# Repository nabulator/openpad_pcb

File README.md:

# openpad_pcb
A pcb for home DIY travelpads, ddr/itg/stepmaniax pads

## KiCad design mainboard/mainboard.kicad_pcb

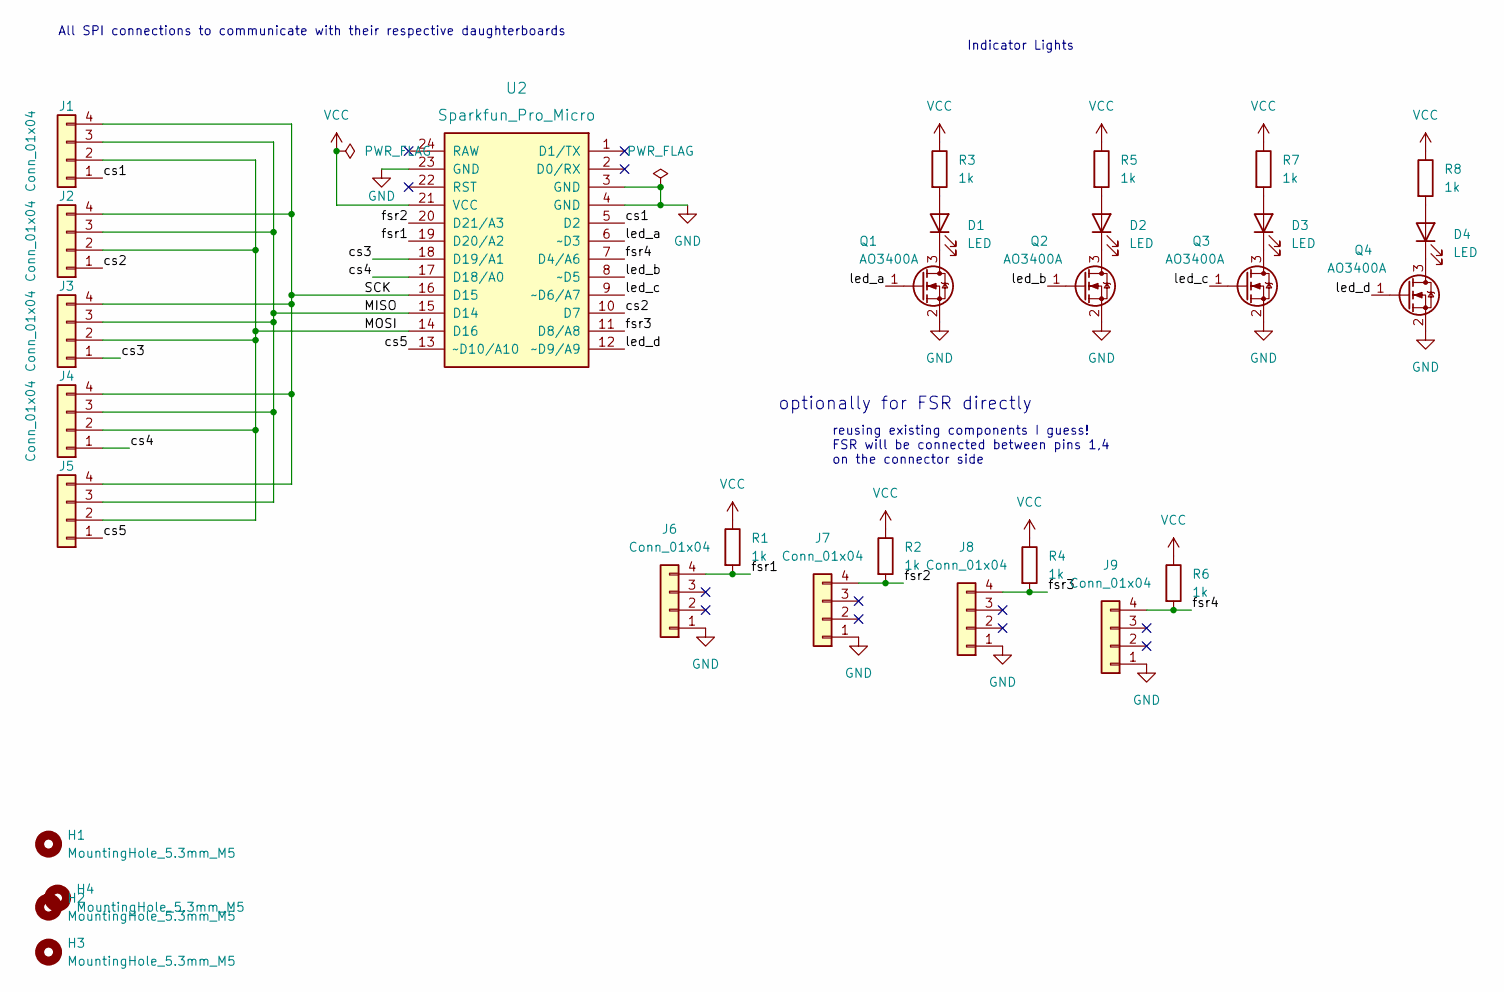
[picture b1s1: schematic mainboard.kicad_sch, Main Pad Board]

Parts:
D1, D2, D3, D4: LED; LED_1210_3225Metric_Pad1.42x2.65mm_HandSolder
H1, H2, H3, H4: MountingHole_5.3mm_M5
J1, J2, J3, J4, J6, J7, J8, J9: Conn_01x04; PinHeader_1x04_P2.54mm_Horizontal
J5: (no value)
Q1, Q2, Q3, Q4: AO3400A; SOT-23
R1, R2, R3, R4, R5, R6, R7, R8: 1k; R_1206_3216Metric_Pad1.30x1.75mm_HandSolder
U2: Sparkfun_Pro_Micro

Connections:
/MISO: J1.3, J2.3, J3.3, J4.3, J5.3, U2.15 (D14)
/MOSI: J1.2, J2.2, J3.2, J4.2, J5.2, U2.14 (D16)
/SCK: J1.4, J2.4, J3.4, J4.4, J5.4, U2.16 (D15)
/cs1: J1.1, U2.5 (D2)
/cs2: J2.1, U2.10 (D7)
/cs3: J3.1, U2.18 (D19/A1)
/cs4: J4.1, U2.17 (D18/A0)
/cs5: J5.1, U2.13 (~D10/A10)
/fsr1: J6.4, R1.2, U2.19 (D20/A2)
/fsr2: J7.4, R2.2, U2.20 (D21/A3)
/fsr3: J8.4, R4.2, U2.11 (D8/A8)
/fsr4: J9.4, R6.2, U2.7 (D4/A6)
/led_a: Q1.1 (G), U2.6 (~D3)
/led_b: Q2.1 (G), U2.8 (~D5)
/led_c: Q3.1 (G), U2.9 (~D6/A7)
/led_d: Q4.1 (G), U2.12 (~D9/A9)
GND: J6.1, J7.1, J8.1, J9.1, Q1.2 (S), Q2.2 (S), Q3.2 (S), Q4.2 (S), U2.3 (GND), U2.4 (GND), U2.23 (GND)
unnamed: D1.1 (K), Q1.3 (D)
unnamed: D1.2 (A), R3.2
unnamed: D2.1 (K), Q2.3 (D)
unnamed: D2.2 (A), R5.2
unnamed: D3.1 (K), Q3.3 (D)
unnamed: D3.2 (A), R7.2
unnamed: D4.1 (K), Q4.3 (D)
unnamed: D4.2 (A), R8.2
VCC: R1.1, R2.1, R3.1, R4.1, R5.1, R6.1, R7.1, R8.1, U2.21 (VCC)

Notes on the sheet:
optionally for FSR directly
All SPI connections to communicate with their respective daughterboards
Indicator Lights
reusing existing components I guess! FSR will be connected between pins 1,4 on the connector side

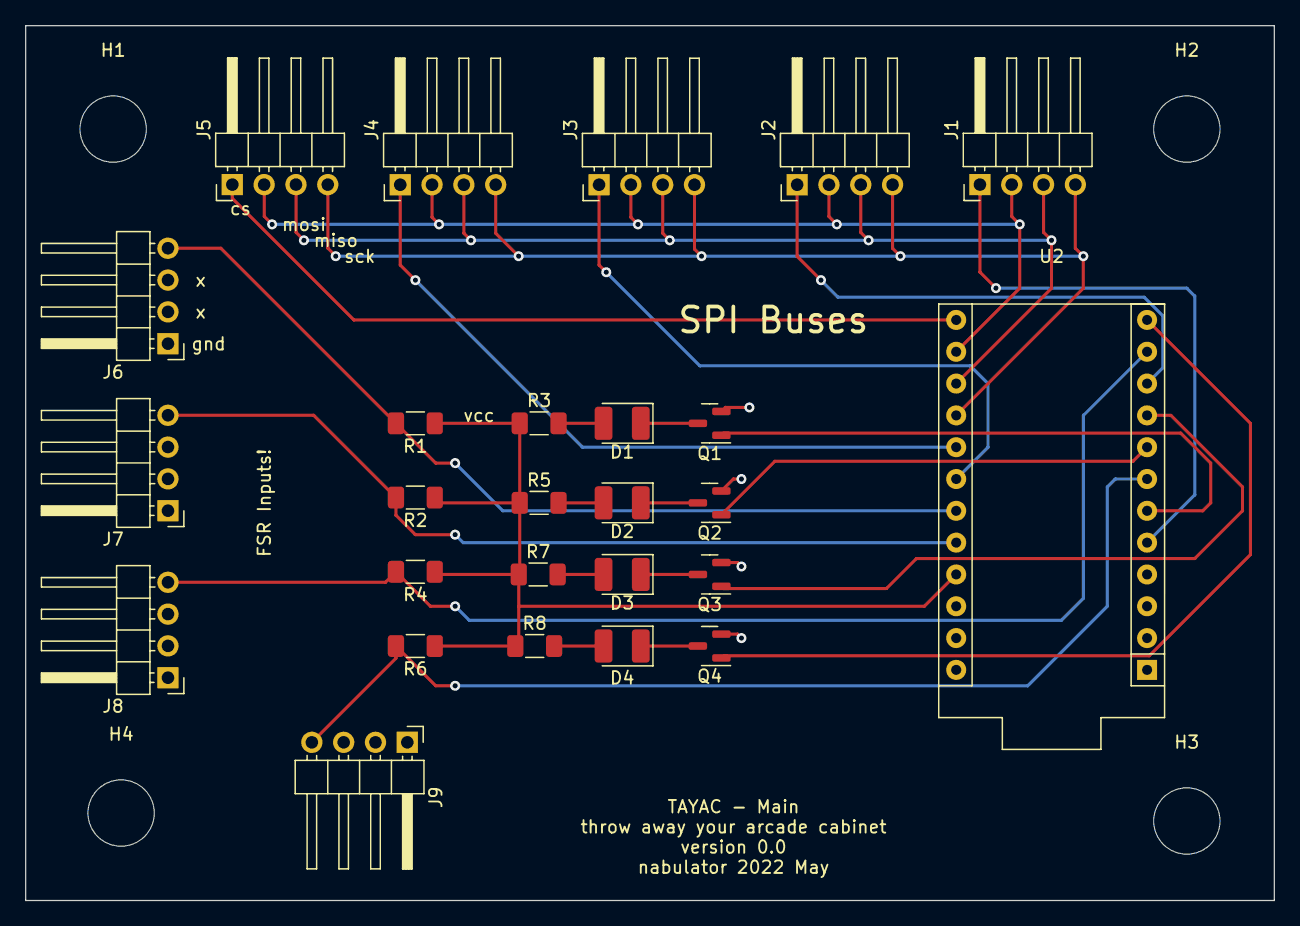
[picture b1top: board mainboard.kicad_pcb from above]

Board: 2 copper layers, 99.7 x 69.8 mm, 31 parts (1 on the bottom side), 26 nets.

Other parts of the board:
G1: LOGO; arrow_graphic

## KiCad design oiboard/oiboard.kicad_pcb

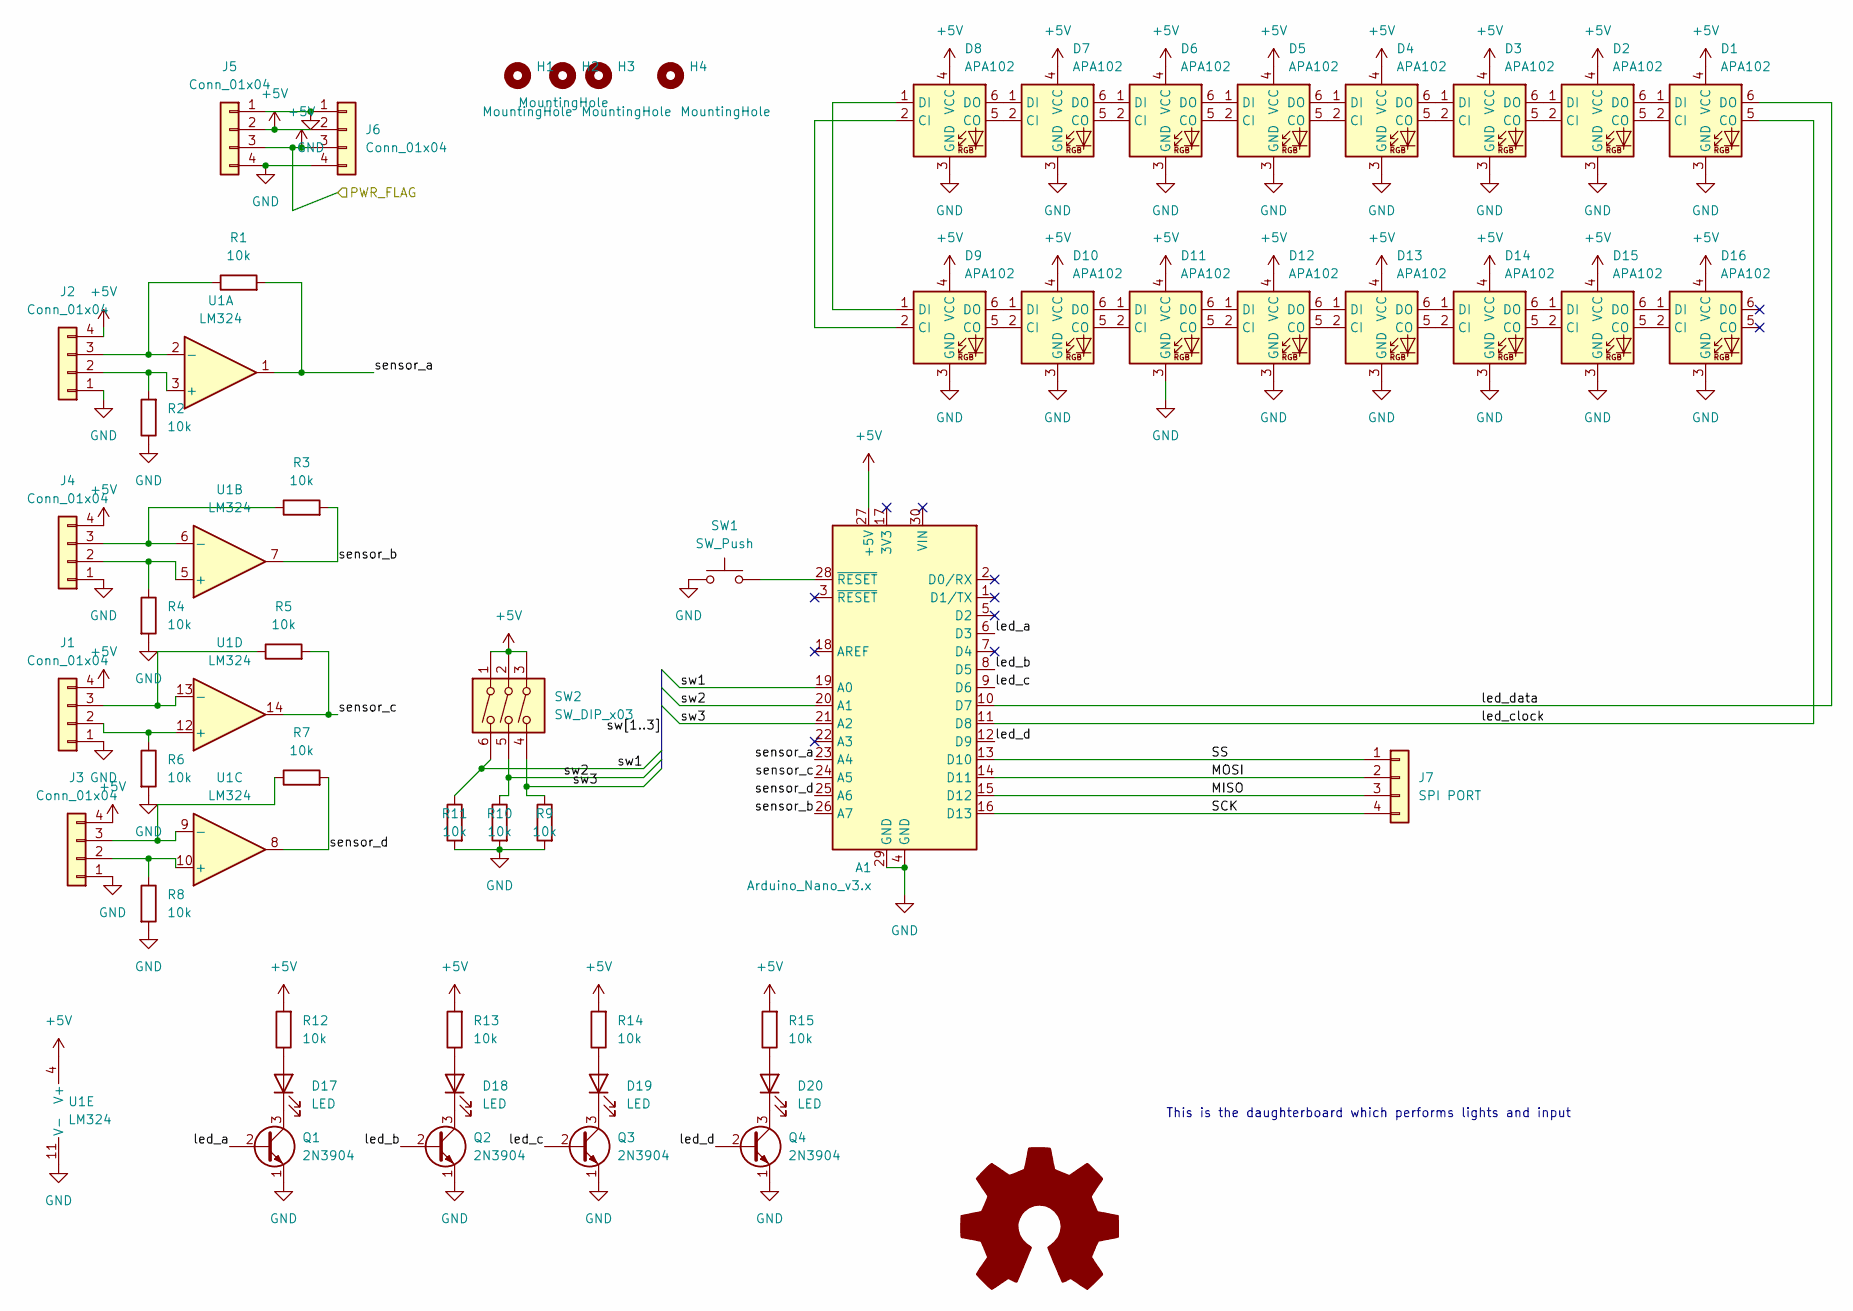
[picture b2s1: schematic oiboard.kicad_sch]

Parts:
A1: Arduino_Nano_v3.x; Arduino_Nano
D1, D2, D3, D4, D5, D6, D7, D8, D9, D10, D11, D12, D13, D14, D15, D16: APA102; LED_RGB_5050-6
D17, D18, D19, D20: LED; LED_D5.0mm
H1, H2, H3, H4: MountingHole; MountingHole_3mm
J1, J2, J3, J4: Conn_01x04; PinHeader_1x04_P2.54mm_Horizontal
J5, J6: Conn_01x04; TerminalBlock_bornier-4_P5.08mm
J7: SPI PORT; PinHeader_1x04_P2.54mm_Horizontal
Q1, Q2, Q3, Q4: 2N3904; TO-92_Inline
R1, R2, R3, R4, R5, R6, R7, R8, R9, R10, R11, R12, R13, R14, R15: 10k; R_Axial_DIN0207_L6.3mm_D2.5mm_P10.16mm_Horizontal
SW1: SW_Push; SW_PUSH_6mm
SW2: SW_DIP_x03; SW_DIP_SPSTx03_Slide_9.78x9.8mm_W7.62mm_P2.54mm
U1: LM324; DIP-14_W7.62mm

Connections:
+5V: A1.27 (+5V), D1.4 (VCC), D2.4 (VCC), D3.4 (VCC), D4.4 (VCC), D5.4 (VCC), D6.4 (VCC), D7.4 (VCC), D8.4 (VCC), D9.4 (VCC), D10.4 (VCC), D11.4 (VCC), D12.4 (VCC), D13.4 (VCC), D14.4 (VCC), D15.4 (VCC), D16.4 (VCC), J1.4, J2.4, J3.4, J4.4, J5.2, J5.3, J6.2, J6.3, R12.2, R13.2, R14.2, R15.2, SW2.1, SW2.2, SW2.3, U1.4 (V+)
/MISO: A1.15 (D12), J7.3
/MOSI: A1.14 (D11), J7.2
/SCK: A1.16 (D13), J7.4
/SS: A1.13 (D10), J7.1
/led_a: A1.6 (D3), Q1.2 (B)
/led_b: A1.8 (D5), Q2.2 (B)
/led_c: A1.9 (D6), Q3.2 (B)
/led_clock: A1.11 (D8), D1.5 (CO)
/led_d: A1.12 (D9), Q4.2 (B)
/led_data: A1.10 (D7), D1.6 (DO)
/sensor_a: A1.23 (A4), R1.2, U1.1
/sensor_b: A1.26 (A7), R3.2, U1.7
/sensor_c: A1.24 (A5), R5.2, U1.14
/sensor_d: A1.25 (A6), R7.2, U1.8
/sw1: A1.19 (A0), R11.1, SW2.6
/sw2: A1.20 (A1), R10.1, SW2.5
/sw3: A1.21 (A2), R9.1, SW2.4
GND: A1.4 (GND), A1.29 (GND), D1.3 (GND), D2.3 (GND), D3.3 (GND), D4.3 (GND), D5.3 (GND), D6.3 (GND), D7.3 (GND), D8.3 (GND), D9.3 (GND), D10.3 (GND), D11.3 (GND), D12.3 (GND), D13.3 (GND), D14.3 (GND), D15.3 (GND), D16.3 (GND), J1.1, J2.1, J3.1, J4.1, J5.1, J5.4, J6.1, J6.4, Q1.1 (E), Q2.1 (E), Q3.1 (E), Q4.1 (E), R2.1, R4.2, R6.2, R8.2, R9.2, R10.2, R11.2, SW1.1, U1.11 (V-)
unnamed: A1.28 (~RESET), SW1.2
unnamed: D1.1 (DI), D2.6 (DO)
unnamed: D1.2 (CI), D2.5 (CO)
unnamed: D2.1 (DI), D3.6 (DO)
unnamed: D2.2 (CI), D3.5 (CO)
unnamed: D3.1 (DI), D4.6 (DO)
unnamed: D3.2 (CI), D4.5 (CO)
unnamed: D4.1 (DI), D5.6 (DO)
unnamed: D4.2 (CI), D5.5 (CO)
unnamed: D5.1 (DI), D6.6 (DO)
unnamed: D5.2 (CI), D6.5 (CO)
unnamed: D6.1 (DI), D7.6 (DO)
unnamed: D6.2 (CI), D7.5 (CO)
unnamed: D7.1 (DI), D8.6 (DO)
unnamed: D7.2 (CI), D8.5 (CO)
unnamed: D8.1 (DI), D9.1 (DI)
unnamed: D8.2 (CI), D9.2 (CI)
unnamed: D9.6 (DO), D10.1 (DI)
unnamed: D9.5 (CO), D10.2 (CI)
unnamed: D10.5 (CO), D11.2 (CI)
unnamed: D10.6 (DO), D11.1 (DI)
unnamed: D11.5 (CO), D12.2 (CI)
unnamed: D11.6 (DO), D12.1 (DI)
unnamed: D12.5 (CO), D13.2 (CI)
unnamed: D12.6 (DO), D13.1 (DI)
unnamed: D13.5 (CO), D14.2 (CI)
unnamed: D13.6 (DO), D14.1 (DI)
unnamed: D14.5 (CO), D15.2 (CI)
unnamed: D14.6 (DO), D15.1 (DI)
unnamed: D15.5 (CO), D16.2 (CI)
unnamed: D15.6 (DO), D16.1 (DI)
unnamed: D17.1 (K), Q1.3 (C)
unnamed: D17.2 (A), R12.1
unnamed: D18.1 (K), Q2.3 (C)
unnamed: D18.2 (A), R13.1
unnamed: D19.1 (K), Q3.3 (C)
unnamed: D19.2 (A), R14.1
unnamed: D20.1 (K), Q4.3 (C)
unnamed: D20.2 (A), R15.1
unnamed: J1.2, R6.1, U1.12 (+)
unnamed: J1.3, R5.1, U1.13 (-)
unnamed: J2.2, R2.2, U1.3 (+)
unnamed: J2.3, R1.1, U1.2 (-)
unnamed: J3.2, R8.1, U1.10 (+)
unnamed: J3.3, R7.1, U1.9 (-)
unnamed: J4.2, R4.1, U1.5 (+)
unnamed: J4.3, R3.1, U1.6 (-)

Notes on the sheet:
This is the daughterboard which performs lights and input

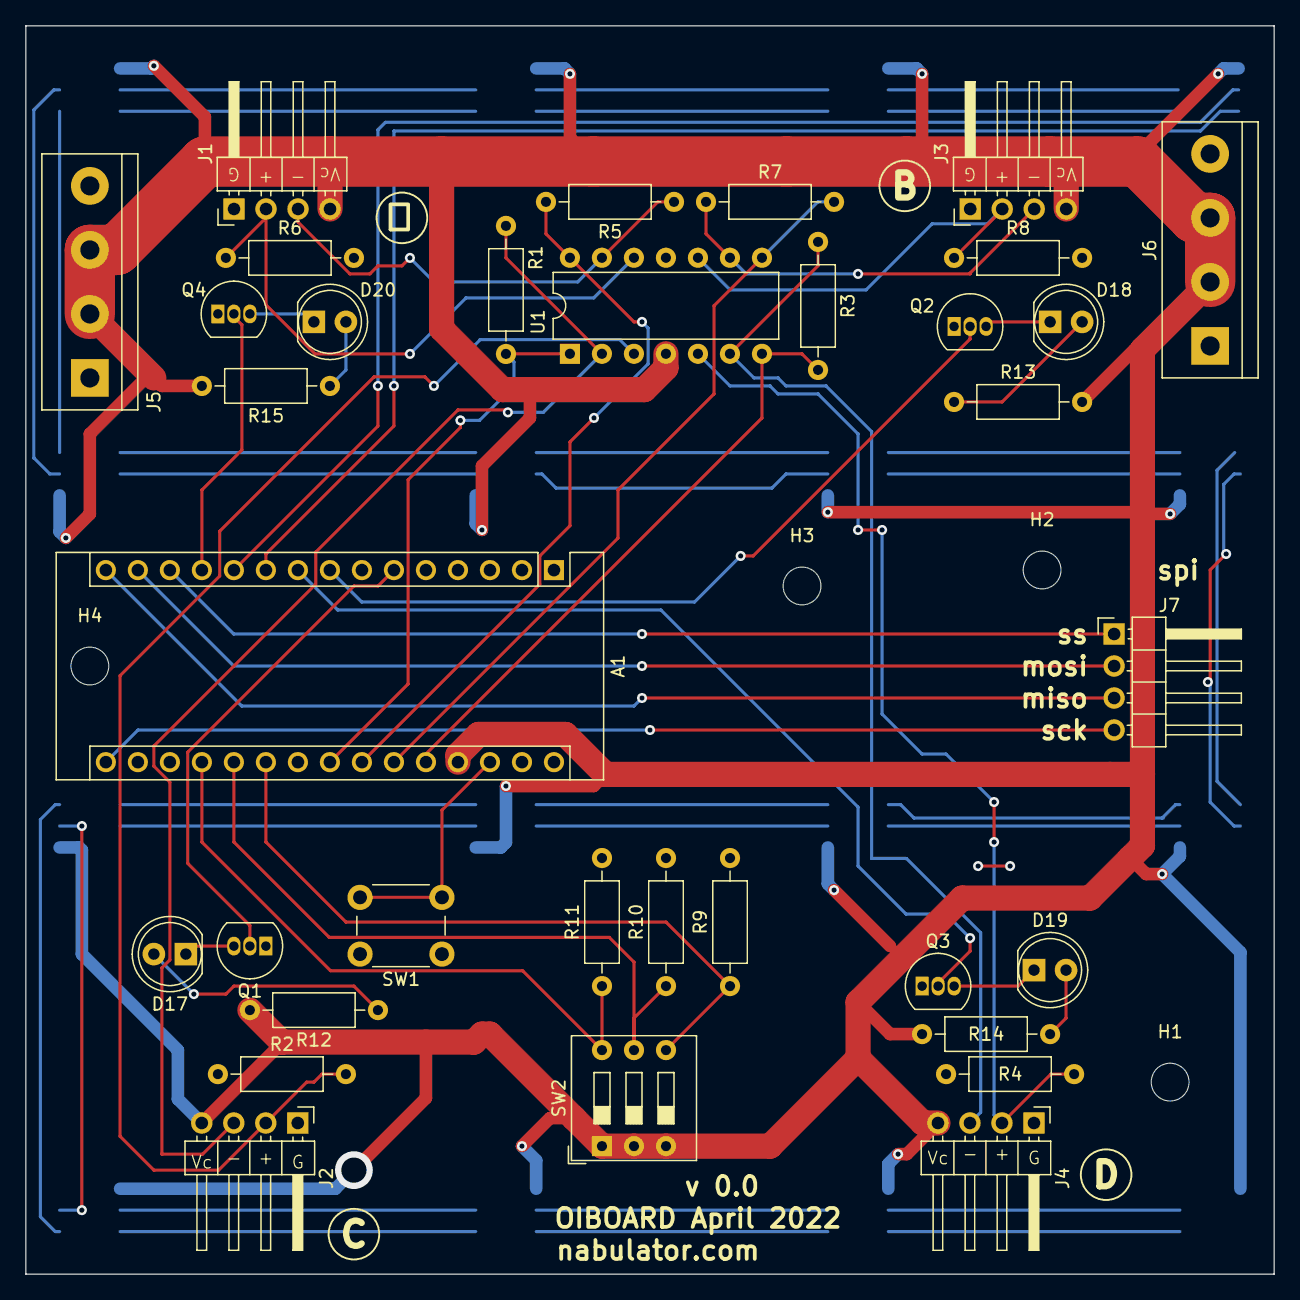
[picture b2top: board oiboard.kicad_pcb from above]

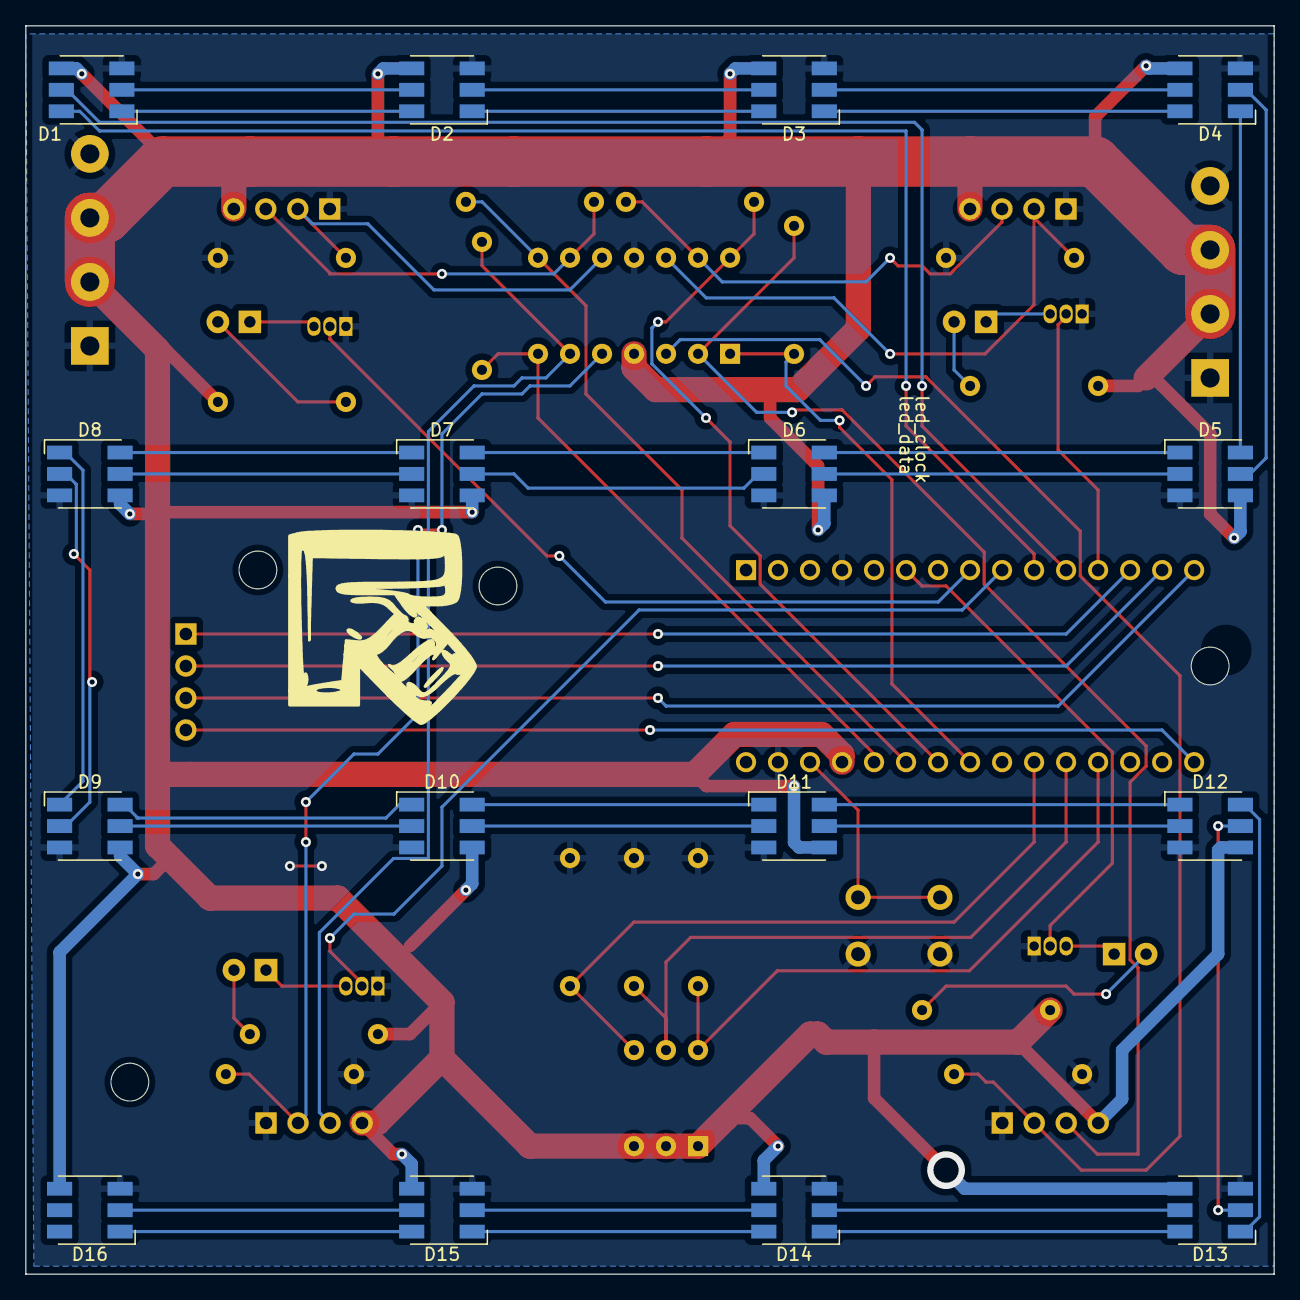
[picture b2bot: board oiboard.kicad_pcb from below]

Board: 2 copper layers, 99.1 x 99.1 mm, 54 parts (16 on the bottom side), 66 nets.

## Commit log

2022-04-06 ignore kicad related crap
2022-04-16 feat: initial commit
2022-04-18 feat: finalize the board layout
2022-04-20 add premlimarp PCB layout
2022-04-23 finalize pcb design 0.0
2022-04-24 add logo to board
2022-05-04 comment
2022-05-04 feat: add arrow graphic
2022-05-04 add git submodules for Arduino Pro micro module
2022-05-05 add additional labels to the daughter oiboard
2022-05-05 initial schematic for main board
2022-05-06 feat: finish the layout of mainboard
2022-05-06 feat: nichijou graphics
